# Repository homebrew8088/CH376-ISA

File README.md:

# CH376 ISA
 CH376 on ISA card with BIOS ext

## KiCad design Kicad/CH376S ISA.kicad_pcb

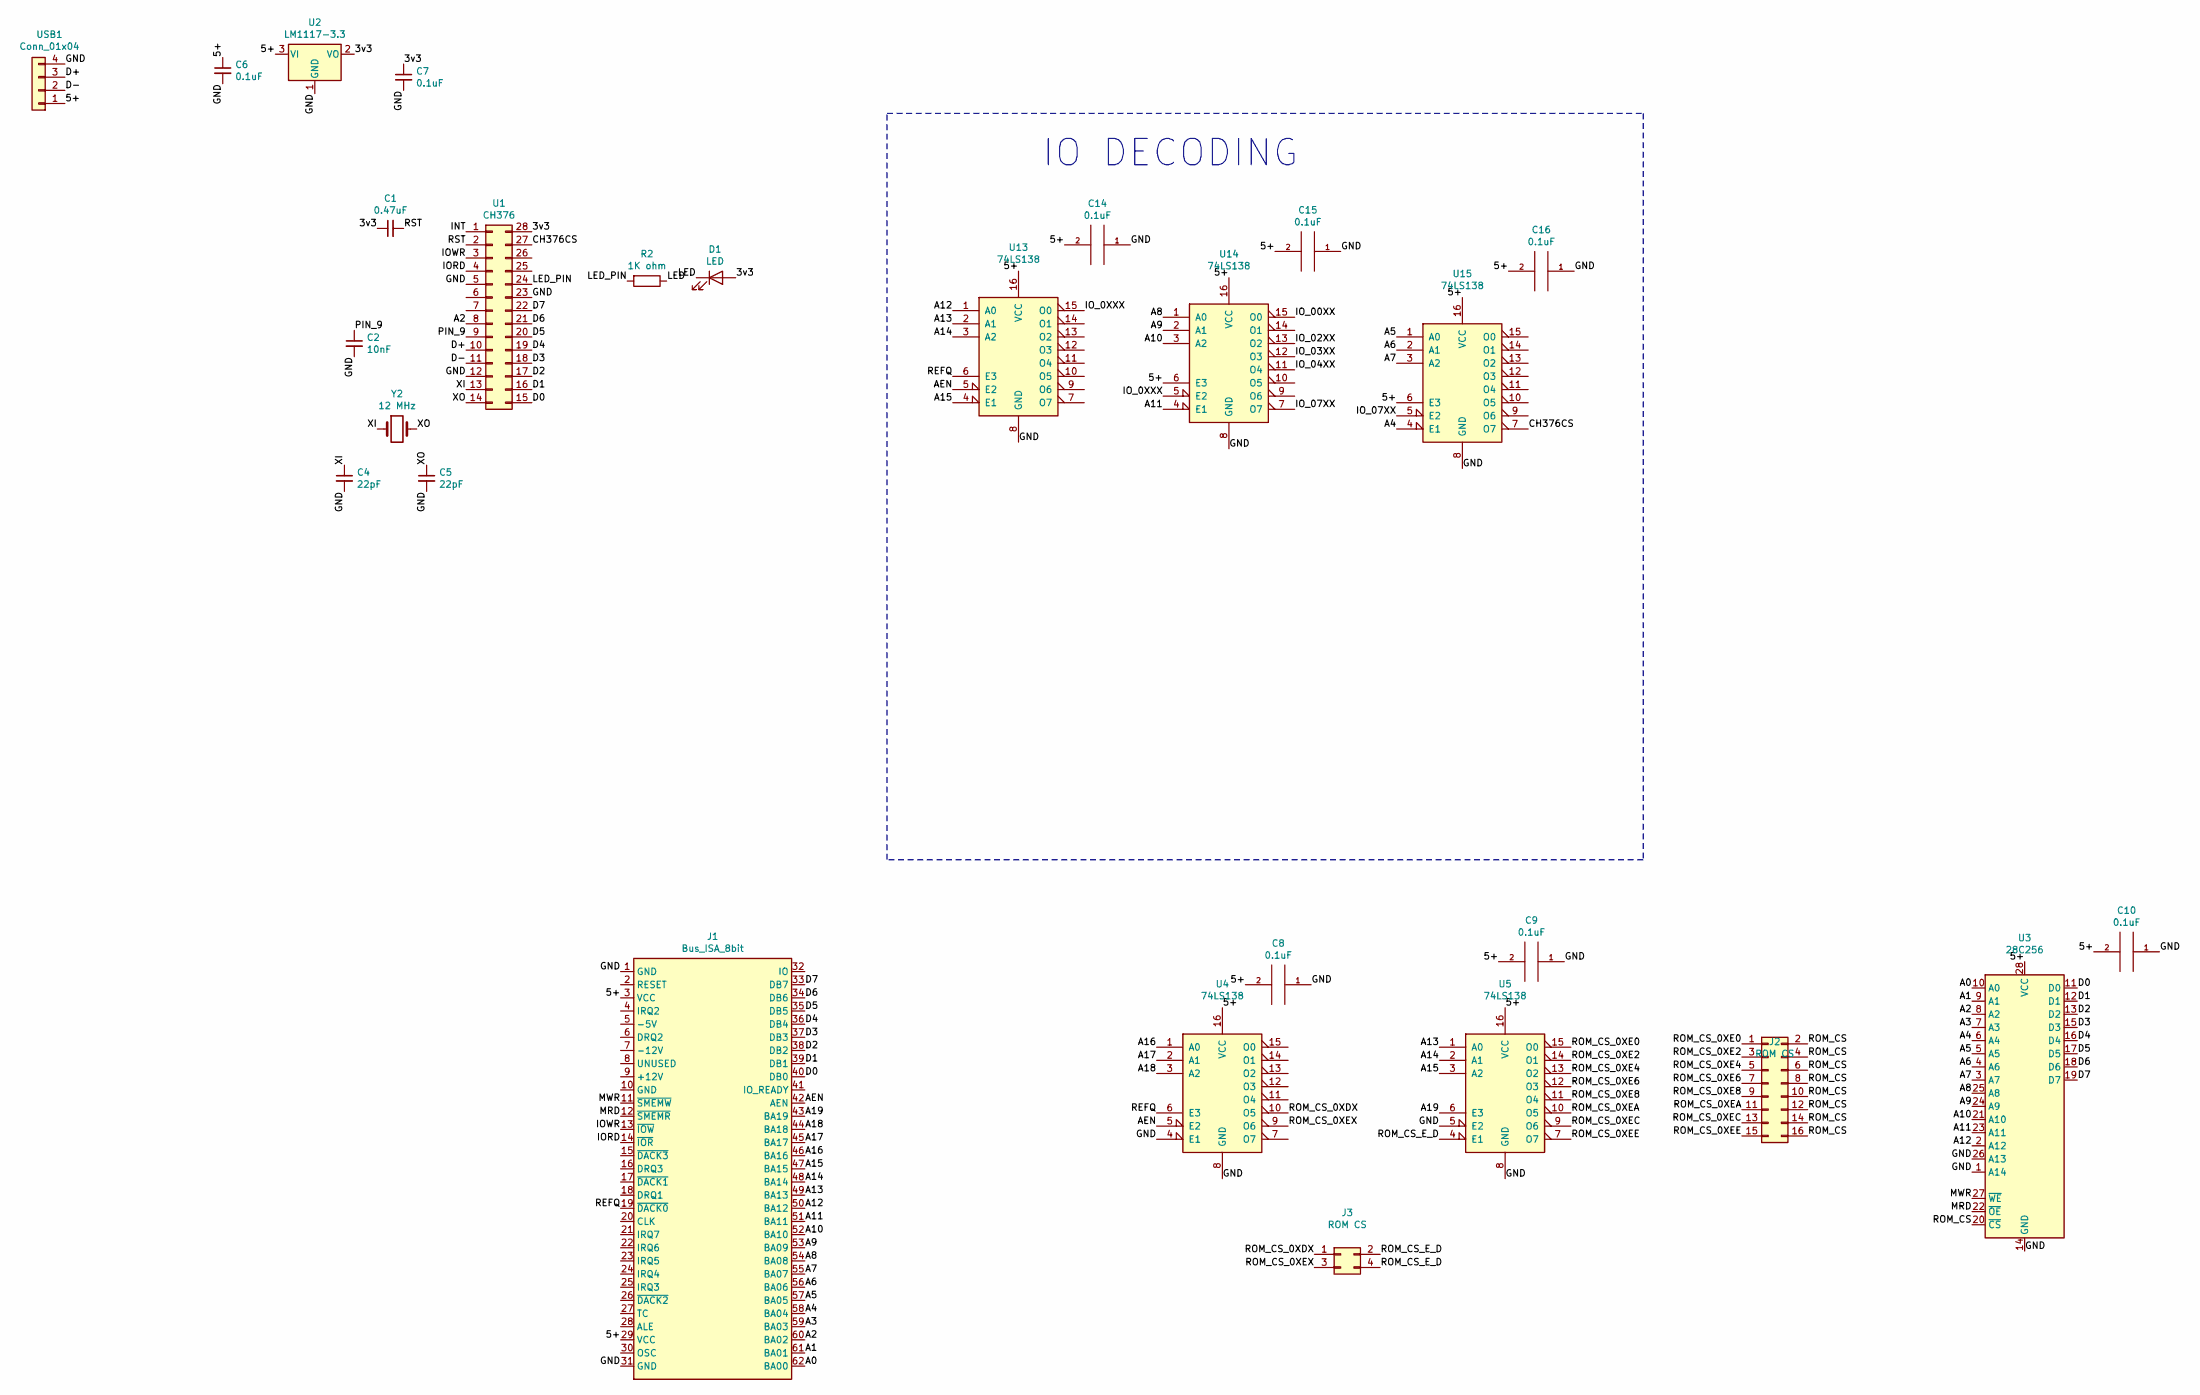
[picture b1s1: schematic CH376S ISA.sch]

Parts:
C1: 0.47uF; C_Disc_D4.3mm_W1.9mm_P5.00mm
C2: 10nF; C_Disc_D4.3mm_W1.9mm_P5.00mm
C4, C5: 22pF; C_Disc_D4.3mm_W1.9mm_P5.00mm
C6, C7, C8, C9, C10, C14, C15, C16: 0.1uF; C_Disc_D4.3mm_W1.9mm_P5.00mm
D1: LED; LED_D3.0mm
J1: Bus_ISA_8bit; BUS_8_BIT
J2: ROM CS; PinHeader_2x08_P2.54mm_Vertical
J3: ROM CS; PinHeader_2x02_P2.54mm_Vertical
R2: 1K ohm; R_Axial_DIN0207_L6.3mm_D2.5mm_P10.16mm_Horizontal
U1: CH376; SOIC-28W_7.5x17.9mm_P1.27mm
U2: LM1117-3.3; TO-220-3_Horizontal_TabDown
U3: 28C256; DIP-28_W15.24mm
U4, U5, U13, U14, U15: 74LS138; DIP-16_W7.62mm
USB1: Conn_01x04; USB_A_CONNFLY_DS1095-WNR0
Y2: 12 MHz; Crystal_HC18-U_Vertical

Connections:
/3v3: C1.1, C7.1, D1.2 (A), U1.28, U2.2 (VO)
/5+: C6.1, C8.2, C9.2, C10.2, C14.2, C15.2, C16.2, J1.3 (VCC), J1.29 (VCC), U2.3 (VI), U3.28 (VCC), U4.16 (VCC), U5.16 (VCC), U13.16 (VCC), U14.6 (E3), U14.16 (VCC), U15.6 (E3), U15.16 (VCC), USB1.1
/A0: J1.62 (BA00), U3.10 (A0)
/A1: J1.61 (BA01), U3.9 (A1)
/A2: J1.60 (BA02), U1.8, U3.8 (A2)
/A3: J1.59 (BA03), U3.7 (A3)
/A4: J1.58 (BA04), U3.6 (A4), U15.4 (E1)
/A5: J1.57 (BA05), U3.5 (A5), U15.1 (A0)
/A6: J1.56 (BA06), U3.4 (A6), U15.2 (A1)
/A7: J1.55 (BA07), U3.3 (A7), U15.3 (A2)
/A8: J1.54 (BA08), U3.25 (A8), U14.1 (A0)
/A9: J1.53 (BA09), U3.24 (A9), U14.2 (A1)
/A10: J1.52 (BA10), U3.21 (A10), U14.3 (A2)
/A11: J1.51 (BA11), U3.23 (A11), U14.4 (E1)
/A12: J1.50 (BA12), U3.2 (A12), U13.1 (A0)
/A13: J1.49 (BA13), U5.1 (A0), U13.2 (A1)
/A14: J1.48 (BA14), U5.2 (A1), U13.3 (A2)
/A15: J1.47 (BA15), U5.3 (A2), U13.4 (E1)
/A16: J1.46 (BA16), U4.1 (A0)
/A17: J1.45 (BA17), U4.2 (A1)
/A18: J1.44 (BA18), U4.3 (A2)
/A19: J1.43 (BA19), U5.6 (E3)
/AEN: J1.42 (AEN), U4.5 (E2), U13.5 (E2)
/CH376CS: U1.27, U15.7 (O7)
/D0: J1.40 (DB0), U1.15, U3.11 (D0)
/D1: J1.39 (DB1), U1.16, U3.12 (D1)
/D2: J1.38 (DB2), U1.17, U3.13 (D2)
/D3: J1.37 (DB3), U1.18, U3.15 (D3)
/D4: J1.36 (DB4), U1.19, U3.16 (D4)
/D5: J1.35 (DB5), U1.20, U3.17 (D5)
/D6: J1.34 (DB6), U1.21, U3.18 (D6)
/D7: J1.33 (DB7), U1.22, U3.19 (D7)
/D+: U1.10, USB1.3
/D-: U1.11, USB1.2
/GND: C2.2, C4.2, C5.2, C6.2, C7.2, C8.1, C9.1, C10.1, C14.1, C15.1, C16.1, J1.1 (GND), J1.31 (GND), U1.5, U1.12, U1.23, U2.1 (GND), U3.1 (A14), U3.14 (GND), U3.26 (A13), U4.4 (E1), U4.8 (GND), U5.5 (E2), U5.8 (GND), U13.8 (GND), U14.8 (GND), U15.8 (GND), USB1.4
/INT: U1.1
/IORD: J1.14 (~IOR), U1.4
/IOWR: J1.13 (~IOW), U1.3
/IO_00XX: U14.15 (O0)
/IO_0XXX: U13.15 (O0), U14.5 (E2)
/IO_02XX: U14.13 (O2)
/IO_03XX: U14.12 (O3)
/IO_04XX: U14.11 (O4)
/IO_07XX: U14.7 (O7), U15.5 (E2)
/LED: D1.1 (K), R2.1
/LED_PIN: R2.2, U1.24
/MRD: J1.12 (~SMEMR), U3.22 (~OE)
/MWR: J1.11 (~SMEMW), U3.27 (~WE)
/PIN_9: C2.1, U1.9
/REFQ: J1.19 (~DACK0), U4.6 (E3), U13.6 (E3)
/ROM_CS: J2.2, J2.4, J2.6, J2.8, J2.10, J2.12, J2.14, J2.16, U3.20 (~CS)
/ROM_CS_0XDX: J3.1, U4.10 (O5)
/ROM_CS_0XE0: J2.1, U5.15 (O0)
/ROM_CS_0XE2: J2.3, U5.14 (O1)
/ROM_CS_0XE4: J2.5, U5.13 (O2)
/ROM_CS_0XE6: J2.7, U5.12 (O3)
/ROM_CS_0XE8: J2.9, U5.11 (O4)
/ROM_CS_0XEA: J2.11, U5.10 (O5)
/ROM_CS_0XEC: J2.13, U5.9 (O6)
/ROM_CS_0XEE: J2.15, U5.7 (O7)
/ROM_CS_0XEX: J3.3, U4.9 (O6)
/ROM_CS_E_D: J3.2, J3.4, U5.4 (E1)
/RST: C1.2, U1.2
/XI: C4.1, U1.13, Y2.1
/XO: C5.1, U1.14, Y2.2

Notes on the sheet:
IO DECODING

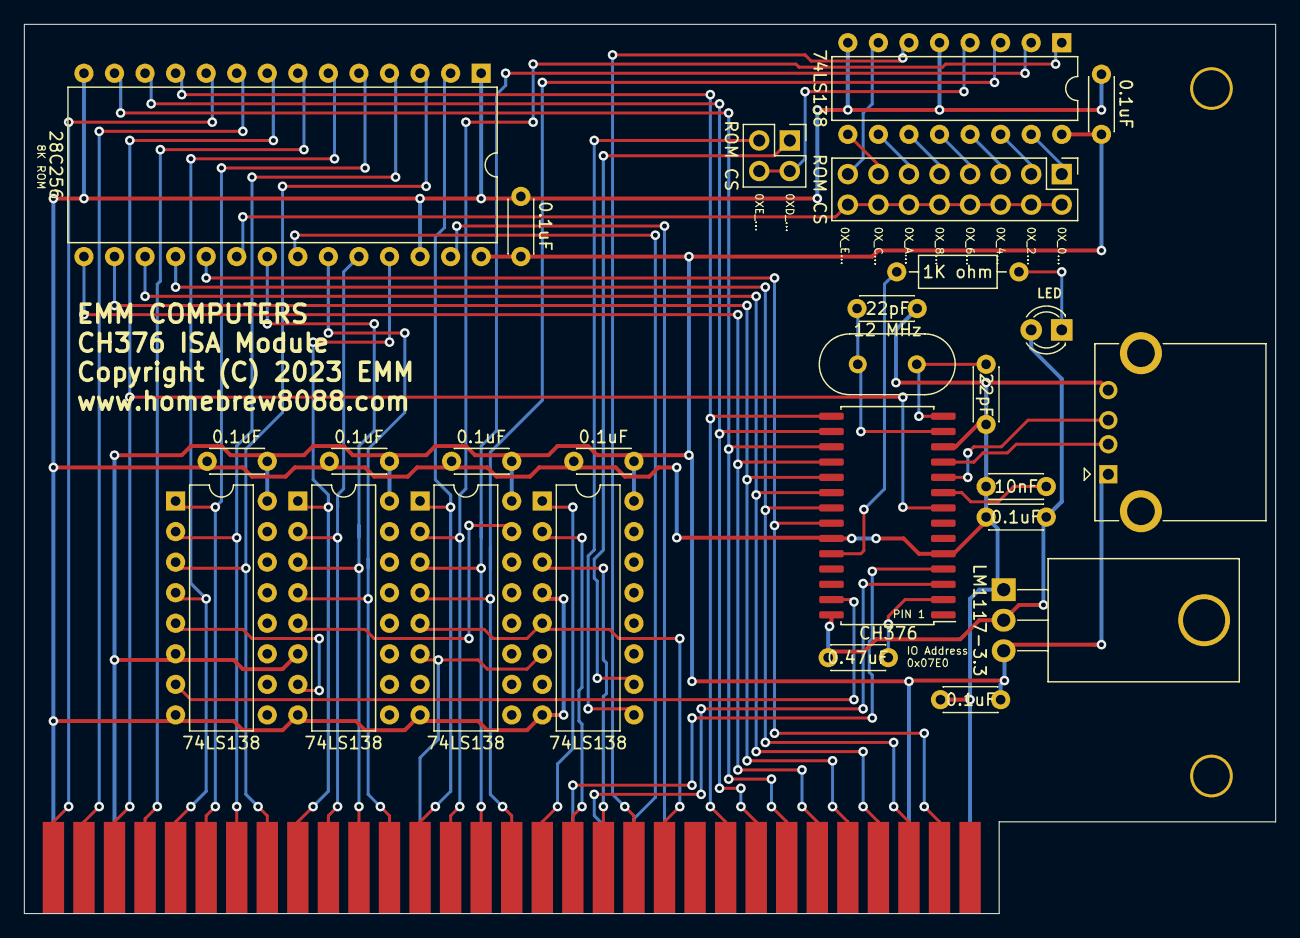
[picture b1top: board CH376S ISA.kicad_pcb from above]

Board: 2 copper layers, 104.0 x 73.9 mm, 29 parts (0 on the bottom side), 60 nets.

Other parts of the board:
R: L; Large_Via
R#2: L; Large_Via

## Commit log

2023-04-09 initial post
2023-05-08 first draft done
2023-05-08 Widen trace
2023-06-13 Changed IO address to 0x07E0
2023-07-27 change
2023-07-28 Added code files

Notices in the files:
Kicad/CH376S ISA.kicad_pcb:
Copyright (C) 2023 EMM
